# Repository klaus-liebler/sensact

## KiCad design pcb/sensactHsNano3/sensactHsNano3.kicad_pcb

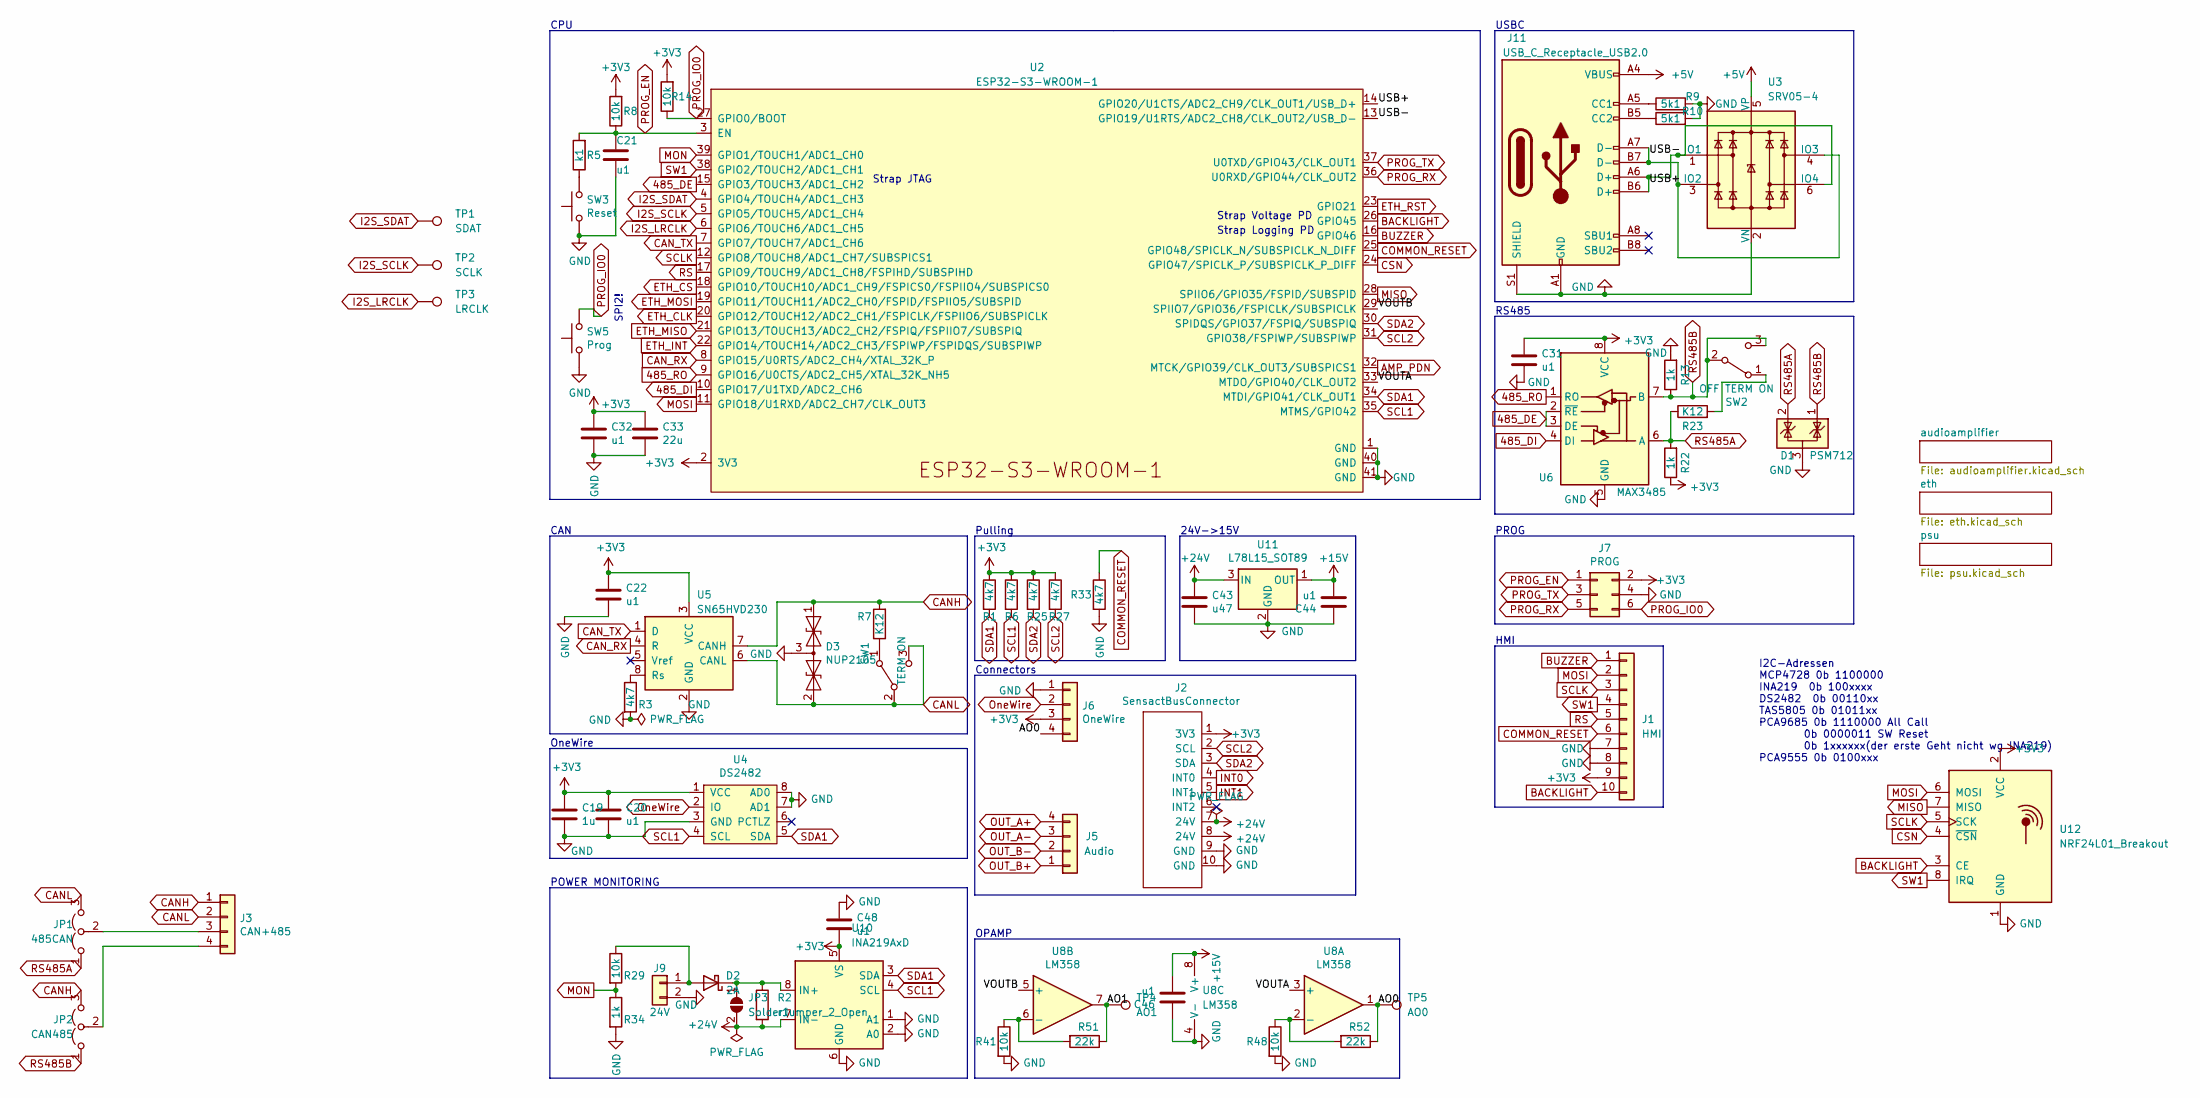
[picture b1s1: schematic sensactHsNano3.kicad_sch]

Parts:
C19: 1u; C_0805_2012Metric_Pad1.18x1.45mm_HandSolder
C20, C48: u1; C_0805_2012Metric_Pad1.18x1.45mm_HandSolder
C21, C22, C31, C32, C44, C46: u1; C_0402_1005Metric
C33: 22u; C_0603_1608Metric
C43: u47; C_0805_2012Metric
D1: PSM712; SOT-23_Handsoldering
D2: 2A; D_SMB_Handsoldering
D3: NUP2105; SOT-23_Handsoldering
J1: HMI; Hirose_FH12-10S-0.5SH_1x10-1MP_P0.50mm_Horizontal
J2: SensactBusConnector; IDC-Header_2x05_P2.54mm_Horizontal_tightCrtYd
J3: CAN+485; PhoenixContact_MC_1,5_4-G-3.5_1x04_P3.50mm_Horizontal_small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
J5: Audio; PhoenixContact_MC_1,5_4-G-3.5_1x04_P3.50mm_Horizontal_small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
J6: OneWire; PhoenixContact_MC_1,5_4-G-3.5_1x04_P3.50mm_Horizontal_small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
J7: PROG; IDC_2x03_P1.27mm_Vertical
J9: 24V; PhoenixContact_MC_1,5_2-G-3.81_1x02_P3.81mm_Horizontal_smal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
J11: USB_C_Receptacle_USB2.0; USB_C_Receptacle_HRO_TYPE-C-31-M-12_smaller
JP1: 485CAN; SolderJumper-3_P1.3mm_Open_RoundedPad1.0x1.5mm_NumberLabels
JP2: CAN485; SolderJumper-3_P1.3mm_Open_RoundedPad1.0x1.5mm_NumberLabels
JP3: SolderJumper_2_Open; SolderJumper-2_P1.3mm_Open_RoundedPad1.0x1.5mm
R1, R3, R6, R25, R27, R33: 4k7; R_0402_1005Metric
R2: r1; R_1206_3216Metric_Pad1.30x1.75mm_HandSolder
R5: k1; R_0402_1005Metric
R7, R23: K12; R_1206_3216Metric_Pad1.30x1.75mm_HandSolder
R8, R14, R29, R41, R48: 10k; R_0402_1005Metric
R9, R10: 5k1; R_0402_1005Metric
R13, R22: 1k; R_0603_1608Metric
R34: 1k; R_0402_1005Metric
R51, R52: 22k; R_0402_1005Metric
SW1: TERM ON; SW_SPDT_PCM12_handsolder
SW2: OFF TERM ON; SW_SPDT_PCM12_handsolder
SW3: Reset; Button_2x4x3,5_handsolder
SW5: Prog; Button_2x4x3,5_handsolder
TP1: SDAT; TestPoint_Pad_2.0x2.0mm
TP2: SCLK; TestPoint_Pad_2.0x2.0mm
TP3: LRCLK; TestPoint_Pad_2.0x2.0mm
TP4: AO1; TestPoint_Pad_2.0x2.0mm
TP5: AO0; TestPoint_Pad_2.0x2.0mm
U2: ESP32-S3-WROOM-1; ESP32-S3-WROOM-1U
U3: SRV05-4; SOT-23-6
U4: DS2482; SOIC-8_3.9x4.9mm_Pitch1.27mm_handsolder
U5: SN65HVD230; SOIC-8_3.9x4.9mm_Pitch1.27mm_handsolder
U6: MAX3485; SOIC-8_3.9x4.9mm_Pitch1.27mm_handsolder
U8: LM358; SOIC-8_3.9x4.9mm_P1.27mm
U10: INA219AxD; SOIC-8_3.9x4.9mm_Pitch1.27mm_handsolder
U11: L78L15_SOT89; SOT-89-3_Handsoldering
U12: NRF24L01_Breakout; nRF24L01_Breakout

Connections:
485_DE: U2.15 (GPIO3/TOUCH3/ADC1_CH2), U6.2 (~RE), U6.3 (DE)
485_DI: U2.10 (GPIO17/U1TXD/ADC2_CH6), U6.4 (DI)
485_RO: U2.9 (GPIO16/U0CTS/ADC2_CH5/XTAL_32K_NH5), U6.1 (RO)
+3V3: C19.1, C20.1, C22.1, C31.2, C32.1, C33.1, C48.2, J1.9, J2.1 (3V3), J6.3, J7.2, R1.1, R6.1, R8.2, R14.2, R22.1, R25.1, R27.1, U2.2 (3V3), U4.1 (VCC), U5.3 (VCC), U6.8 (VCC), U10.5 (VS), U12.2 (VCC); also elsewhere on the board
+5V: J11.A4 (VBUS), J11.A9 (VBUS), J11.B4 (VBUS), J11.B9 (VBUS), U3.5 (VP)
+15V: C44.2, C46.2, U8.8 (V+), U11.1 (OUT)
+24V: C43.1, J2.7 (24V), J2.8 (24V), JP3.2 (B), R2.2, U10.7 (IN-), U11.3 (IN); also elsewhere on the board
/AO0: J6.4, R52.1, TP5.1, U8.1
/AO1: R51.1, TP4.1, U8.7
/USB+: J11.A6 (D+), J11.B6 (D+), U2.14 (GPIO20/U1CTS/ADC2_CH9/CLK_OUT1/USB_D+), U3.1 (IO1), U3.6 (IO4)
/USB-: J11.A7 (D-), J11.B7 (D-), U2.13 (GPIO19/U1RTS/ADC2_CH8/CLK_OUT2/USB_D-), U3.3 (IO2), U3.4 (IO3)
/VOUTA: U2.33 (MTDO/GPIO40/CLK_OUT2), U8.3 (+)
/VOUTB: U2.29 (SPIIO7/GPIO36/FSPICLK/SUBSPICLK), U8.5 (+)
AMP_PDN: U2.32 (MTCK/GPIO39/CLK_OUT3/SUBSPICS1); also elsewhere on the board
BACKLIGHT: J1.10, U2.26 (GPIO45), U12.3 (CE)
BUZZER: J1.1, U2.16 (GPIO46)
CANH: D3.1 (A1), J3.1, JP2.3 (B), R7.2, U5.7 (CANH)
CANL: D3.2 (A2), J3.2, JP1.3 (B), SW1.2 (B), SW1.3 (C), U5.6 (CANL)
CAN_RX: U2.8 (GPIO15/U0RTS/ADC2_CH4/XTAL_32K_P), U5.4 (R)
CAN_TX: U2.7 (GPIO7/TOUCH7/ADC1_CH6), U5.1 (D)
COMMON_RESET: J1.6, R33.1, U2.25 (GPIO48/SPICLK_N/SUBSPICLK_N_DIFF)
CSN: U2.24 (GPIO47/SPICLK_P/SUBSPICLK_P_DIFF), U12.4 (~CSN)
ETH_CLK: U2.20 (GPIO12/TOUCH12/ADC2_CH1/FSPICLK/FSPIIO6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); also elsewhere on the board
ETH_CS: U2.18 (GPIO10/TOUCH10/ADC1_CH9/FSPICS0/FSPIIO4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); also elsewhere on the board
ETH_INT: U2.22 (GPIO14/TOUCH14/ADC2_CH3/FSPIWP/FSPIDQS/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); also elsewhere on the board
ETH_MISO: U2.21 (GPIO13/TOUCH13/ADC2_CH2/FSPIQ/FSPIIO7/S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); also elsewhere on the board
ETH_MOSI: U2.19 (GPIO11/TOUCH11/ADC2_CH0/FSPID/FSPIIO5/S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); also elsewhere on the board
ETH_RST: U2.23 (GPIO21); also elsewhere on the board
GND: C19.2, C20.2, C21.2, C22.2, C31.1, C32.2, C33.2, C43.2, C44.1, C46.1, C48.1, D1.3 (A), D3.3 (common), J1.7, J1.8, J2.9 (GND), J2.10 (GND), J6.1, J7.4, J9.2, J11.A1 (GND), J11.A12 (GND), J11.B1 (GND), J11.B12 (GND), J11.S1 (SHIELD), R3.2, R9.2, R10.2, R13.2, R33.2, R34.2, R41.2, R48.2, SW3.1, SW5.1, U2.1 (GND), U2.40 (GND), U2.41 (GND), U3.2 (VN), U4.3 (GND), U4.7 (AD1), U4.8 (AD0), U5.2 (GND), U6.5 (GND), U8.4 (V-), U10.1 (A1), U10.2 (A0), U10.6 (GND), U11.2 (GND), U12.1 (GND); also elsewhere on the board
I2S_LRCLK: TP3.1, U2.6 (GPIO6/TOUCH6/ADC1_CH5); also elsewhere on the board
I2S_SCLK: TP2.1, U2.5 (GPIO5/TOUCH5/ADC1_CH4); also elsewhere on the board
I2S_SDAT: TP1.1, U2.4 (GPIO4/TOUCH4/ADC1_CH3); also elsewhere on the board
INT0: J2.4 (INT0)
INT1: J2.5 (INT1)
MISO: U2.28 (SPIIO6/GPIO35/FSPID/SUBSPID), U12.7 (MISO)
MON: R29.2, R34.1, U2.39 (GPIO1/TOUCH1/ADC1_CH0)
MOSI: J1.2, U2.11 (GPIO18/U1RXD/ADC2_CH7/CLK_OUT3), U12.6 (MOSI)
unnamed: D2.2 (A), J9.1, R29.1
unnamed: D2.1 (K), JP3.1 (A), R2.1, U10.8 (IN+)
unnamed: J3.3, JP1.2 (C)
unnamed: J3.4, JP2.2 (C)
unnamed: J11.A5 (CC1), R9.1
unnamed: J11.B5 (CC2), R10.1
unnamed: R5.1, SW3.2
unnamed: R7.1, SW1.1 (A)
unnamed: R23.2, SW2.1 (A)
unnamed: R3.1, U5.8 (Rs)
unnamed: R48.1, R52.2, U8.2 (-)
unnamed: R41.1, R51.2, U8.6 (-)
OUT_A+: J5.4; also elsewhere on the board
OUT_A-: J5.3; also elsewhere on the board
OUT_B+: J5.1; also elsewhere on the board
OUT_B-: J5.2; also elsewhere on the board
OneWire: J6.2, U4.2 (IO)
PROG_EN: C21.1, J7.1, R5.2, R8.1, U2.3 (EN)
PROG_IO0: J7.6, R14.1, SW5.2, U2.27 (GPIO0/BOOT)
PROG_RX: J7.5, U2.36 (U0RXD/GPIO44/CLK_OUT2)
PROG_TX: J7.3, U2.37 (U0TXD/GPIO43/CLK_OUT1)
RS: J1.5, U2.17 (GPIO9/TOUCH9/ADC1_CH8/FSPIHD/SUBSPIHD)
RS485A: D1.2 (K), JP1.1 (A), R22.2, R23.1, U6.6 (A)
RS485B: D1.1 (K), JP2.1 (A), R13.1, SW2.2 (B), SW2.3 (C), U6.7 (B)
SCL1: R6.2, U2.35 (MTMS/GPIO42), U4.4 (SCL), U10.4 (SCL); also elsewhere on the board
SCL2: J2.2 (SCL), R27.2, U2.31 (GPIO38/FSPIWP/SUBSPIWP)
SCLK: J1.3, U2.12 (GPIO8/TOUCH8/ADC1_CH7/SUBSPICS1), U12.5 (SCK)
SDA1: R1.2, U2.34 (MTDI/GPIO41/CLK_OUT1), U4.5 (SDA), U10.3 (SDA); also elsewhere on the board
SDA2: J2.3 (SDA), R25.2, U2.30 (SPIDQS/GPIO37/FSPIQ/SUBSPIQ)
SW1: J1.4, U2.38 (GPIO2/TOUCH2/ADC1_CH1), U12.8 (IRQ)

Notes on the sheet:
OneWire
Strap JTAG
Connectors
I2C-Adressen MCP4728 0b 1100000 INA219 0b 100xxxx DS2482 0b 00110xx TAS5805 0b 01011xx PCA9685 0b 1110000 All Call 0b 0000011 SW Reset 0b 1xxxxxx(der erste Geht nicht wg INA219) PCA9555 0b 0100xxx
Strap Voltage PD
HMI
OPAMP
RS485
Pulling
POWER MONITORING
PROG
24V->15V
CAN
SPI2!
USBC
CPU
Strap Logging PD

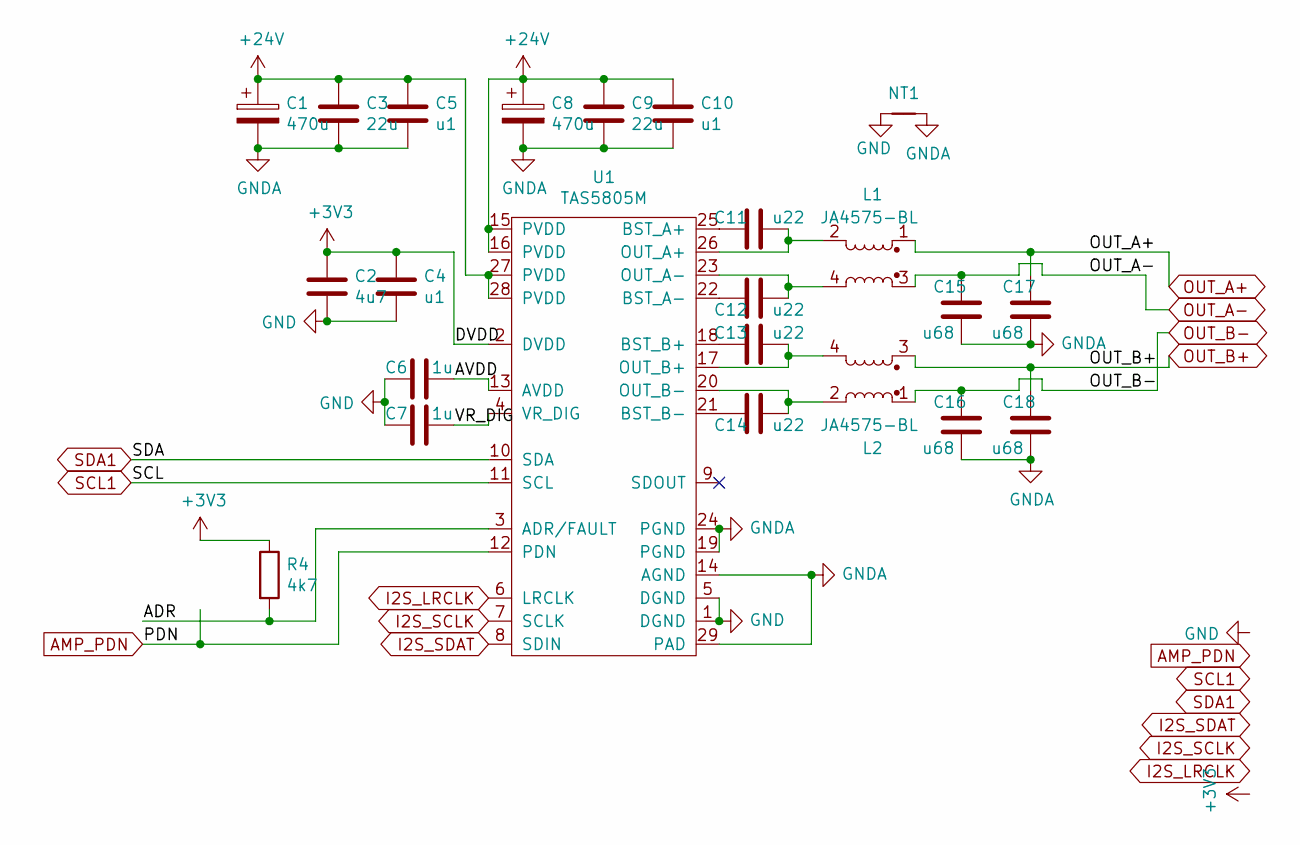
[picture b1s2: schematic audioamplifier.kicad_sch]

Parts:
C1, C8: 470u; CP_Radial_D10.0mm_P3.50mm
C2: 4u7; C_0402_1005Metric
C3, C9: 22u; C_1210_3225Metric_Pad1.33x2.70mm_HandSolder
C4: u1; C_0402_1005Metric
C5, C10: u1; C_0603_1608Metric
C6, C7: 1u; C_0402_1005Metric
C11, C12, C13, C14: u22; C_0603_1608Metric
C15, C16, C17, C18: u68; C_Rect_L7.0mm_W4.5mm_P5.00mm
L1, L2: JA4575-BL
NT1: Net-Tie_2; NetTie-2_SMD_Pad2.0mm
R4: 4k7; R_0402_1005Metric
U1: TAS5805M; HTSSOP-28-1EP_4.4x9.7mm_P0.65mm_EP2.85x5.4mm_ThermalVias

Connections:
+3V3: C2.1, C4.1, R4.1, U1.2 (DVDD); also elsewhere on the board
+24V: C1.1, C3.1, C5.1, C8.1, C9.1, C10.1, U1.15 (PVDD), U1.16 (PVDD), U1.27 (PVDD), U1.28 (PVDD); also elsewhere on the board
/audioamplifier/ADR: R4.2, U1.3 (ADR/FAULT)
/audioamplifier/AVDD: C6.1, U1.13 (AVDD)
/audioamplifier/VR_DIG: C7.1, U1.4 (VR_DIG)
AMP_PDN: U1.12 (PDN); also elsewhere on the board
GND: C2.2, C4.2, C6.2, C7.2, NT1.1, U1.1 (DGND), U1.5 (DGND); also elsewhere on the board
GNDA: C1.2, C3.2, C5.2, C8.2, C9.2, C10.2, C15.1, C16.1, C17.1, C18.1, NT1.2, U1.14 (AGND), U1.19 (PGND), U1.24 (PGND), U1.29 (PAD)
I2S_LRCLK: U1.6 (LRCLK); also elsewhere on the board
I2S_SCLK: U1.7 (SCLK); also elsewhere on the board
I2S_SDAT: U1.8 (SDIN); also elsewhere on the board
unnamed: C11.2, U1.25 (BST_A+)
unnamed: C12.2, U1.22 (BST_A-)
unnamed: C13.2, U1.18 (BST_B+)
unnamed: C14.2, U1.21 (BST_B-)
unnamed: C11.1, L1.2, U1.26 (OUT_A+)
unnamed: C12.1, L1.4, U1.23 (OUT_A-)
unnamed: C13.1, L2.4, U1.17 (OUT_B+)
unnamed: C14.1, L2.2, U1.20 (OUT_B-)
OUT_A+: C17.2, L1.1; also elsewhere on the board
OUT_A-: C15.2, L1.3; also elsewhere on the board
OUT_B+: C18.2, L2.3; also elsewhere on the board
OUT_B-: C16.2, L2.1; also elsewhere on the board
SCL1: U1.11 (SCL); also elsewhere on the board
SDA1: U1.10 (SDA); also elsewhere on the board

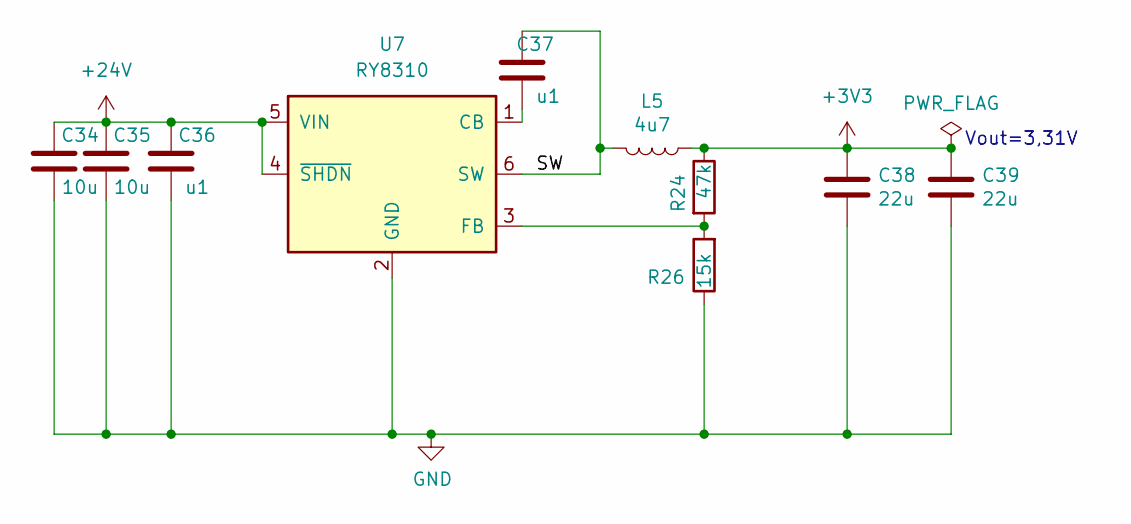
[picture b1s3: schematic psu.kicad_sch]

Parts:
C34, C35: 10u; C_1206_3216Metric
C36, C37: u1; C_0603_1608Metric
C38, C39: 22u; C_0603_1608Metric
L5: 4u7; L_Abracon_ASPI-0630LR
R24: 47k; R_0402_1005Metric
R26: 15k; R_0402_1005Metric
U7: RY8310; SOT-23-6

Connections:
+3V3: C38.1, C39.1, L5.1, R24.1; also elsewhere on the board
+24V: C34.2, C35.2, C36.2, U7.4 (~SHDN), U7.5 (VIN); also elsewhere on the board
/psu/SW: C37.2, L5.2, U7.6 (SW)
GND: C34.1, C35.1, C36.1, C38.2, C39.2, R26.1, U7.2 (GND); also elsewhere on the board
unnamed: C37.1, U7.1 (CB)
unnamed: R24.2, R26.2, U7.3 (FB)

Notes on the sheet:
Vout=3,31V

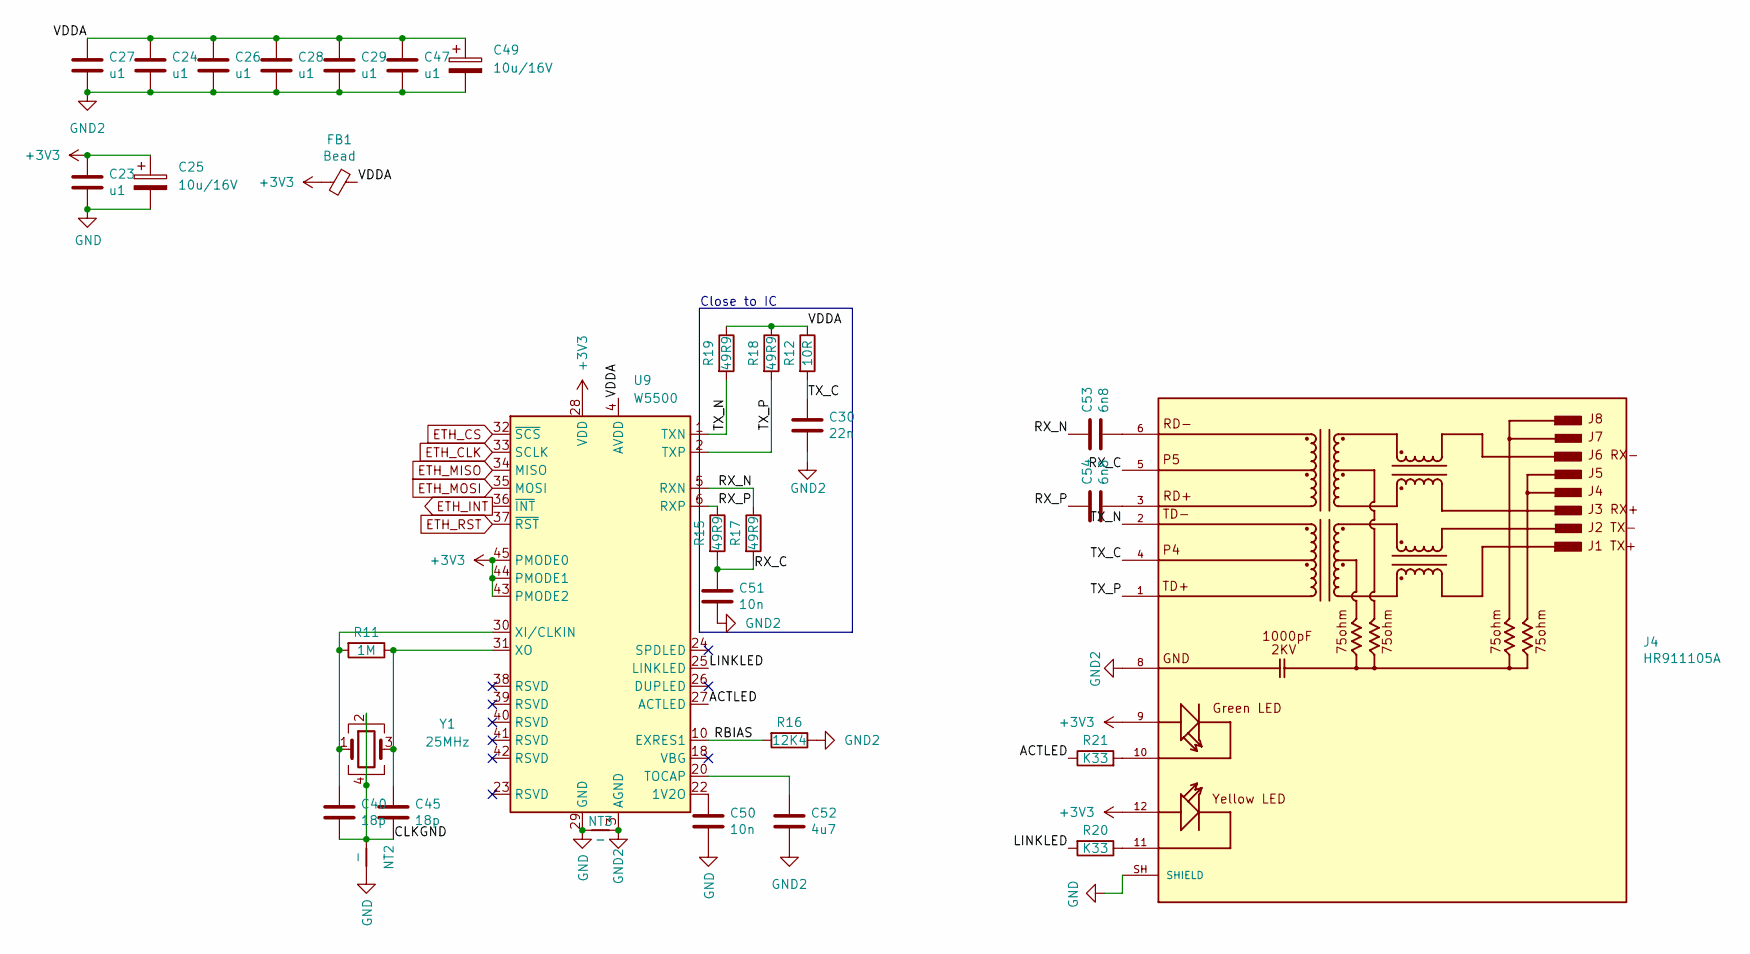
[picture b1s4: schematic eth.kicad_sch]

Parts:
C23, C24, C26, C27, C28, C29, C47: u1; C_0402_1005Metric
C25, C49: 10u/16V; CP_EIA-3216-18_Kemet-A
C30: 22n; C_0402_1005Metric
C40, C45: 18p; C_0402_1005Metric
C50, C51: 10n; C_0402_1005Metric
C52: 4u7; C_0402_1005Metric
C53, C54: 6n8; C_0402_1005Metric
FB1: Bead; L_0805_2012Metric
J4: HR911105A; RJ45_HANRUN_HR911105A; PARTREV A
NT2, NT3: -; NetTie-2_SMD_Pad0.5mm
R11: 1M; R_0402_1005Metric
R12: 10R; R_0402_1005Metric
R15, R17, R18, R19: 49R9; R_0603_1608Metric
R16: 12K4; R_0402_1005Metric
R20, R21: K33; R_0402_1005Metric
U9: W5500; LQFP-48_7x7mm_P0.5mm
Y1: 25MHz; Crystal_SMD_3225-4Pin_3.2x2.5mm

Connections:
+3V3: C23.1, C25.1, FB1.2, J4.9, J4.12, U9.28 (VDD), U9.43 (PMODE2), U9.44 (PMODE1), U9.45 (PMODE0); also elsewhere on the board
/eth/ACTLED: R21.1, U9.27 (ACTLED)
/eth/CLKGND: C40.2, C45.2, NT2.2, Y1.2, Y1.4
/eth/LINKLED: R20.2, U9.25 (LINKLED)
/eth/RBIAS: R16.2, U9.10 (EXRES1)
/eth/RX_C: C51.1, J4.5, R15.2, R17.2
/eth/RX_N: C53.1, R17.1, U9.5 (RXN)
/eth/RX_P: C54.1, R15.1, U9.6 (RXP)
/eth/TX_C: C30.1, J4.4, R12.2
/eth/TX_N: J4.2, R19.2, U9.1 (TXN)
/eth/TX_P: J4.1, R18.2, U9.2 (TXP)
/eth/VDDA: C24.1, C26.1, C27.1, C28.1, C29.1, C47.1, C49.1, FB1.1, R12.1, R18.1, R19.1, U9.4 (AVDD), U9.8 (AVDD), U9.11 (AVDD), U9.15 (AVDD), U9.17 (AVDD), U9.21 (AVDD)
ETH_CLK: U9.33 (SCLK); also elsewhere on the board
ETH_CS: U9.32 (~SCS); also elsewhere on the board
ETH_INT: U9.36 (~INT); also elsewhere on the board
ETH_MISO: U9.34 (MISO); also elsewhere on the board
ETH_MOSI: U9.35 (MOSI); also elsewhere on the board
ETH_RST: U9.37 (~RST); also elsewhere on the board
GND: C23.2, C25.2, C50.2, J4.SH (SHIELD), NT2.1, NT3.2, U9.29 (GND); also elsewhere on the board
GND2: C24.2, C26.2, C27.2, C28.2, C29.2, C30.2, C47.2, C49.2, C51.2, C52.2, J4.8, NT3.1, R16.1, U9.3 (AGND), U9.9 (AGND), U9.14 (AGND), U9.16 (AGND), U9.19 (AGND), U9.48 (AGND)
unnamed: C53.2, J4.6
unnamed: C54.2, J4.3
unnamed: J4.10, R21.2
unnamed: J4.11, R20.1
unnamed: C50.1, U9.22 (1V2O)
unnamed: C52.1, U9.20 (TOCAP)
unnamed: C40.1, R11.2, U9.30 (XI/CLKIN), Y1.1
unnamed: C45.1, R11.1, U9.31 (XO), Y1.3

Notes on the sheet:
Close to IC

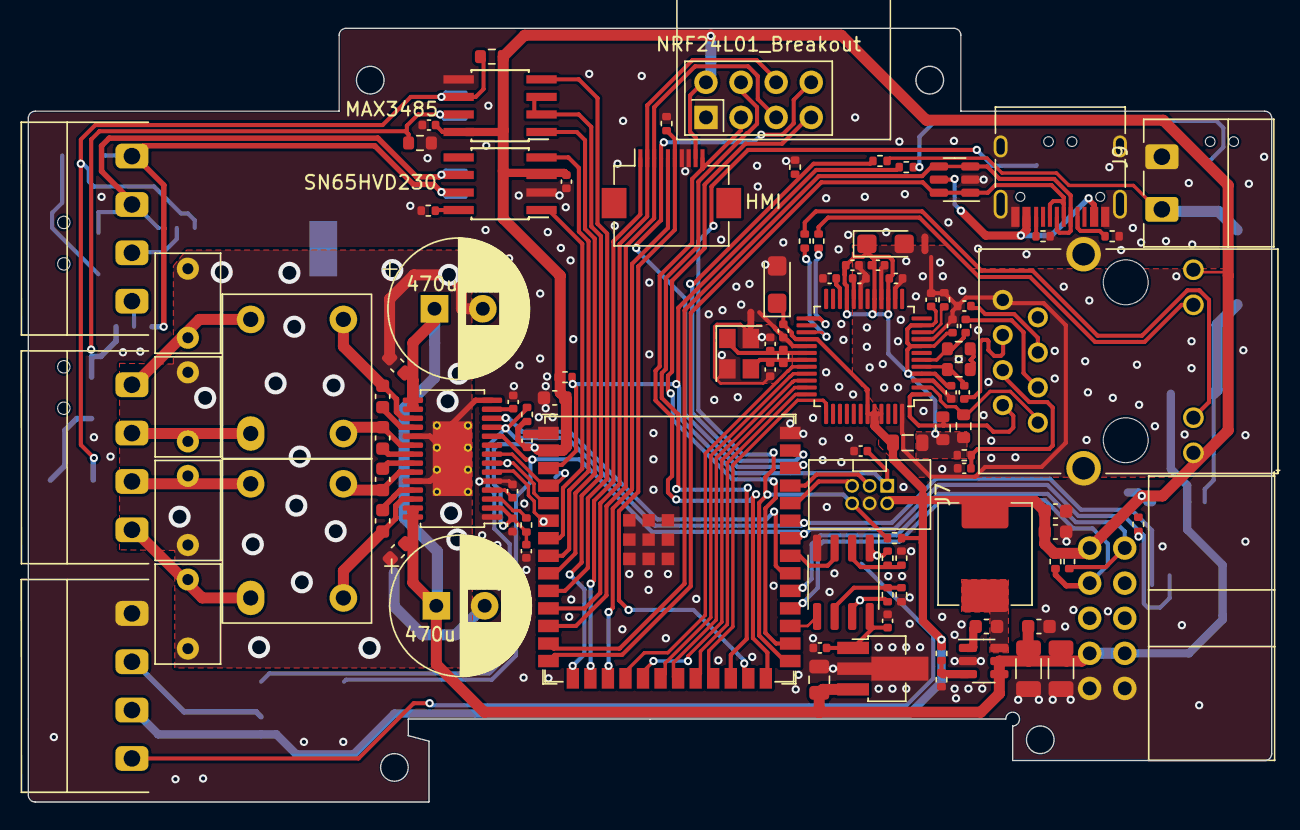
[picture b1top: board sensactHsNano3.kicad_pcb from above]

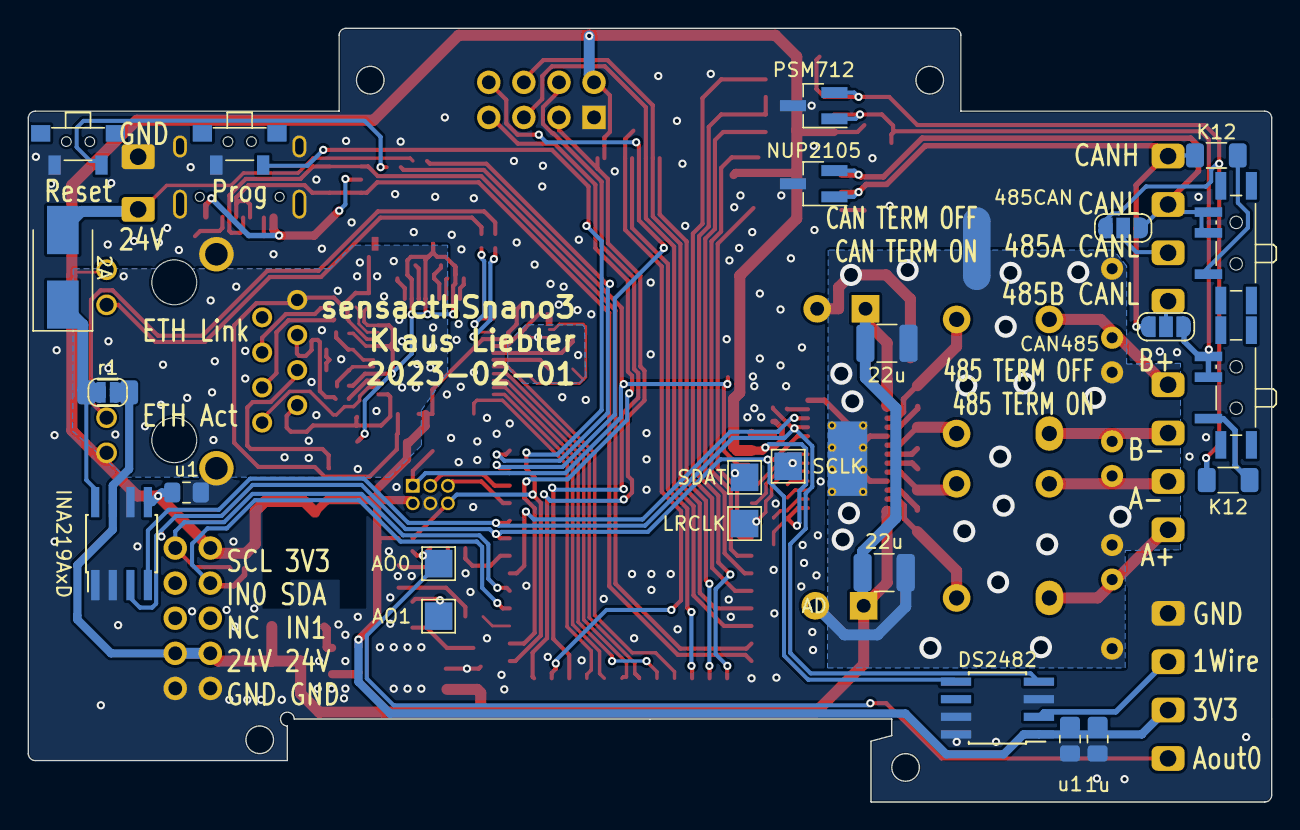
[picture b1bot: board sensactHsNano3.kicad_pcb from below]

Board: 2 copper layers, 90.0 x 56.0 mm, 130 parts (26 on the bottom side), 100 nets.

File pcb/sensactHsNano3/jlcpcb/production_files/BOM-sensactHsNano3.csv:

Comment,Designator,Footprint,LCSC
Bead,FB1,L_0805_2012Metric,C1017
12K4,R16,R_0402_1005Metric,C11692
1k,R34,R_0402_1005Metric,C11702
SN65HVD230,U5,SOIC-8_3.9x4.9mm_Pitch1.27mm_handsolder,C12084
10u,"C34,C35",C_1206_3216Metric,C13585
u47,C43,C_0805_2012Metric,C13967
u1,"C10,C36,C37,C5",C_0603_1608Metric,C14663
10n,"C50,C51",C_0402_1005Metric,C15195
22n,C30,C_0402_1005Metric,C1532
6n8,"C53,C54",C_0402_1005Metric,C1542
18p,"C40,C45",C_0402_1005Metric,C1549
USB_C_Receptacle_USB2.0,J11,USB_C_Receptacle_HRO_TYPE-C-31-M-12_smaller,C165948
u22,"C11,C12,C13,C14",C_0603_1608Metric,C21120
1k,"R13,R22",R_0603_1608Metric,C21190
49R9,"R15,R17,R18,R19",R_0603_1608Metric,C23185
4u7,"C2,C52",C_0402_1005Metric,C23733
k1,R5,R_0402_1005Metric,C25076
10R,R12,R_0402_1005Metric,C25077
K33,"R20,R21",R_0402_1005Metric,C25104
10k,"R14,R29,R41,R48,R8",R_0402_1005Metric,C25744
15k,R26,R_0402_1005Metric,C25756
22k,"R51,R52",R_0402_1005Metric,C25768
47k,R24,R_0402_1005Metric,C25792
4k7,"R1,R25,R27,R3,R33,R4,R6",R_0402_1005Metric,C25900
5k1,"R10,R9",R_0402_1005Metric,C25905
1M,R11,R_0402_1005Metric,C26083
HMI,J1,Hirose_FH12-10S-0.5SH_1x10-1MP_P0.50mm_Horizontal,C262659
ESP32-S3-WROOM-1,U2,ESP32-S3-WROOM-1U,C3013944
u1,"C21,C22,C23,C24,C26,C27,C28,C29,C31,C32,C4,C44,C46,C47",C_0402_1005Metric,C307331
W5500,U9,LQFP-48_7x7mm_P0.5mm,C32843
RY8310,U7,SOT-23-6,C370876
4u7,L5,L_Abracon_ASPI-0630LR,C408447
TAS5805M,U1,HTSSOP-28-1EP_4.4x9.7mm_P0.65mm_EP2.85x5.4mm_ThermalVias,C478472
1u,"C6,C7",C_0402_1005Metric,C52923
22u,"C33,C38,C39",C_0603_1608Metric,C59461
10u/16V,"C25,C49",CP_EIA-3216-18_Kemet-A,C7171
22u,"C3,C9",C_1210_3225Metric_Pad1.33x2.70mm_HandSolder,C778721
LM358,U8,SOIC-8_3.9x4.9mm_P1.27mm,C7950
SRV05-4,U3,SOT-23-6,C85364
MAX3485,U6,SOIC-8_3.9x4.9mm_Pitch1.27mm_handsolder,C8963
25MHz,Y1,Crystal_SMD_3225-4Pin_3.2x2.5mm,C9006
u68,C15,C_Rect_L7.0mm_W4.5mm_P5.00mm,
u68,C16,C_Rect_L7.0mm_W4.5mm_P5.00mm,
u68,C17,C_Rect_L7.0mm_W4.5mm_P5.00mm,
u68,C18,C_Rect_L7.0mm_W4.5mm_P5.00mm,
K12,R7,R_1206_3216Metric_Pad1.30x1.75mm_HandSolder,
OFF TERM  ON,SW2,SW_SPDT_PCM12_handsolder,
TERM ON,SW1,SW_SPDT_PCM12_handsolder,
PSM712,D1,SOT-23_Handsoldering,
NUP2105,D3,SOT-23_Handsoldering,
K12,R23,R_1206_3216Metric_Pad1.30x1.75mm_HandSolder,
Reset,SW3,"Button_2x4x3,5_handsolder",
2A,D2,D_SMB_Handsoldering,
1u,C19,C_0805_2012Metric_Pad1.18x1.45mm_HandSolder,
CAN+485,J3,"PhoenixContact_MC_1,5_4-G-3.5_1x04_P3.50mm_Horizontal_smallerCourtyard",
HR911105A,J4,RJ45_HANRUN_HR911105A,
u1,C20,C_0805_2012Metric_Pad1.18x1.45mm_HandSolder,
JA4575-BL,L2,JA4575-BL,
Audio,J5,"PhoenixContact_MC_1,5_4-G-3.5_1x04_P3.50mm_Horizontal_smallerCourtyard",
JA4575-BL,L1,JA4575-BL,
SensactBusConnector,J2,IDC-Header_2x05_P2.54mm_Horizontal_tightCrtYd,
DS2482,U4,SOIC-8_3.9x4.9mm_Pitch1.27mm_handsolder,
470u,C8,CP_Radial_D10.0mm_P3.50mm,
470u,C1,CP_Radial_D10.0mm_P3.50mm,
Net-Tie_2,NT1,NetTie-2_SMD_Pad2.0mm,
PROG,J7,IDC_2x03_P1.27mm_Vertical,
OneWire,J6,"PhoenixContact_MC_1,5_4-G-3.5_1x04_P3.50mm_Horizontal_smallerCourtyard",
L78L15_SOT89,U11,SOT-89-3_Handsoldering,
24V,J9,"PhoenixContact_MC_1,5_2-G-3.81_1x02_P3.81mm_Horizontal",
-,NT3,NetTie-2_SMD_Pad0.5mm,
NRF24L01_Breakout,U12,nRF24L01_Breakout,
-,NT2,NetTie-2_SMD_Pad0.5mm,
SDAT,TP1,TestPoint_Pad_2.0x2.0mm,
SolderJumper_2_Open,JP3,SolderJumper-2_P1.3mm_Open_RoundedPad1.0x1.5mm,
LRCLK,TP3,TestPoint_Pad_2.0x2.0mm,
AO0,TP5,TestPoint_Pad_2.0x2.0mm,
485CAN,JP1,SolderJumper-3_P1.3mm_Open_RoundedPad1.0x1.5mm_NumberLabels,
SCLK,TP2,TestPoint_Pad_2.0x2.0mm,
Prog,SW5,"Button_2x4x3,5_handsolder",
AO1,TP4,TestPoint_Pad_2.0x2.0mm,
CAN485,JP2,SolderJumper-3_P1.3mm_Open_RoundedPad1.0x1.5mm_NumberLabels,
INA219AxD,U10,SOIC-8_3.9x4.9mm_Pitch1.27mm_handsolder,
r1,R2,R_1206_3216Metric_Pad1.30x1.75mm_HandSolder,
u1,C48,C_0805_2012Metric_Pad1.18x1.45mm_HandSolder,

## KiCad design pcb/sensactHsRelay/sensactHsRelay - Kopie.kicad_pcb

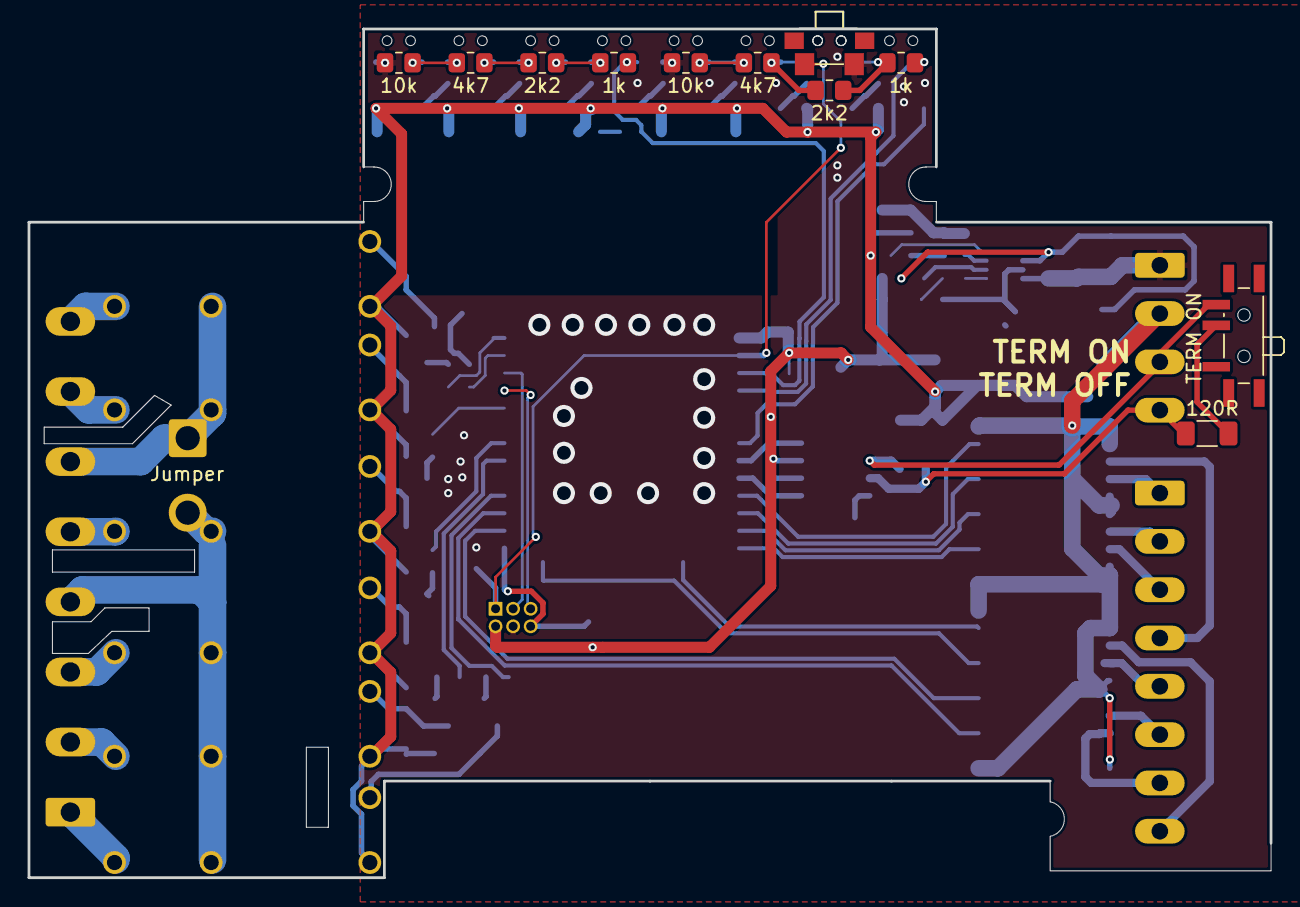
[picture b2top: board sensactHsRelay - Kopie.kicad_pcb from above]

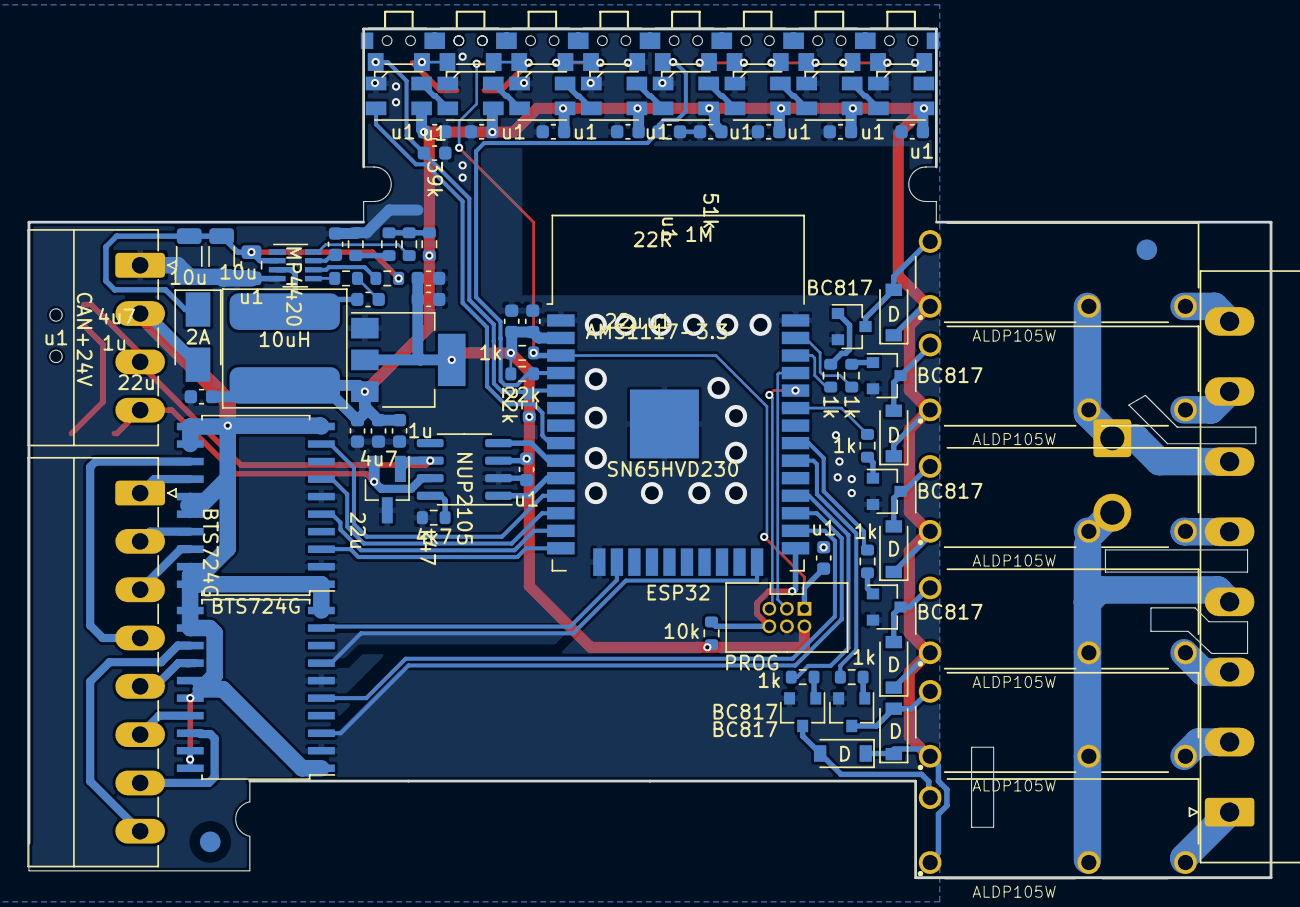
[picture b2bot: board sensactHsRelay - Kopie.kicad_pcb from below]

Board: 2 copper layers, 90.0 x 61.5 mm, 103 parts (91 on the bottom side), 81 nets.

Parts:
C1, C2, C3, C4, C5, C6, C7, C8, C9, C10, C22, C32, C36, C37, C40: u1; C_0603_1608Metric
C11, C14: 4u7; C_0603_1608Metric
C12, C13: 1u; C_0603_1608Metric
C31, C34: 10u; C_1206_3216Metric
C33, C38, C39: 22u; C_0603_1608Metric
C35: u1; C_0805_2012Metric
D1, D2, D5, D6, D7, D8: D; D_SOD-123
D3: NUP2105; SOT-23_Handsoldering
D4: 2A; D_SMA
FID1, FID2: Fiducial; Fiducial_1.5mm_Mask3mm
J1: PROG; IDC_2x03_P1.27mm_Vertical
J2: Conn_01x08; PhoenixContact_MC_1,5_8-G-3.5_1x08_P3.50mm_Horizontal
J3: CAN+24V; PhoenixContact_MC_1,5_4-G-3.5_1x04_P3.50mm_Horizontal
J4: Conn_01x08; PhoenixContact_MSTBA_2,5_8-G-5,08_1x08_P5.08mm_Horizontal
JP3: Jumper; SolderWire-1sqmm_1x02_P5.4mm_D1.4mm_OD2.7mm
K1, K2, K3, K4, K5, K6: ALDP105W; RELAY_ALDP105W
L5: 10uH; ASPIAIG-Q8080
LED1, LED2, LED3, LED4, LED5, LED6, LED7, LED8: SK6812; LED_SK6812MINI_PLCC4_3.5x3.5mm_P1.75mm
PB1, PB2, PB3, PB4, PB5, PB6, PB7, PB8: PB; Button_2x4x3,5
Q1, Q2, Q3, Q4, Q5, Q6: BC817; SOT-23
R2, R10: 22k; R_0603_1608Metric
R3: 4k7; R_0603_1608Metric
R4, R12: 10k; R_0805_2012Metric_Pad1.20x1.40mm_HandSolder
R5, R14: 4k7; R_0805_2012Metric_Pad1.20x1.40mm_HandSolder
R7: 120R; R_1206_3216Metric_Pad1.30x1.75mm_HandSolder
R8, R15: 2k2; R_0805_2012Metric_Pad1.20x1.40mm_HandSolder
R9, R16: 1k; R_0805_2012Metric_Pad1.20x1.40mm_HandSolder
R11, R13, R17, R18, R19, R20, R21: 1k; R_0603_1608Metric
R22: 1M; R_0603_1608Metric
R23: 51k; R_0603_1608Metric
R24: 22R; R_0603_1608Metric
R25: 10k; R_0603_1608Metric
R26: k47; R_0603_1608Metric
R34: 6k8; R_0603_1608Metric
R35: 39k; R_0603_1608Metric
SW1: TERM ON; SW_SPDT_PCM12_handsolder
SW3: Reset; Button_2x4x3,5_handsolder
U1: AMS1117-3.3; SOT-223-3_TabPin2
U2, U4: BTS724G; Infineon_PG-DSO-20-32
U3: ESP32; ESP32-WROOM-32
U5: SN65HVD230; SOIC-8_3.9x4.9mm_P1.27mm
U7: MP4420; TSOT-23-8

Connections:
+3V3: C13.1, C14.1, C22.1, C32.1, C33.1, J1.2, R2.2, R10.2, R11.1, R25.1, U1.2, U3.2, U5.3
+5V: C1.1, C2.1, C3.1, C4.1, C5.1, C6.1, C7.1, C8.1, C11.1, C12.1, C38.1, C39.1, D1.1, D2.1, D5.1, D6.1, D7.1, D8.1, K1.A1, K2.A1, K3.A1, K4.A1, K5.A1, K6.A1, L5.1, LED1.3, LED2.3, LED3.3, LED4.3, LED5.3, LED6.3, LED7.3, LED8.3, R35.1, U1.3
+24V: C31.2, C34.2, C35.2, D4.1, R22.1, U7.2
/EXT1: U3.12, U4.7
/EXT2: U3.13, U4.5
/EXT3: U3.14, U4.3
/EXT4: U3.11, U4.9
/EXT5: U2.7, U3.24
/EXT6: U2.5, U3.26
/EXT7: U2.3, U3.27
/EXT8: U2.9, U3.16
/psu/SW: C37.1, L5.2, U7.3
CANH: D3.2, J3.4, R7.2, U5.7
CANL: D3.1, J3.3, SW1.3, U5.6
CAN_RX: U3.9, U5.4
CAN_TX: U3.10, U5.1
GND: C1.2, C2.2, C3.2, C4.2, C5.2, C6.2, C7.2, C8.2, C9.1, C10.1, C11.2, C12.2, C13.2, C14.2, C22.2, C31.1, C32.2, C33.2, C34.1, C35.1, C36.1, C38.2, C39.2, C40.2, D3.3, J1.4, J3.1, LED1.1, LED2.1, LED3.1, LED4.1, LED5.1, LED6.1, LED7.1, LED8.1, PB1.2, PB5.2, Q1.2, Q2.2, Q3.2, Q4.2, Q5.2, Q6.2, R3.2, R4.1, R12.1, R34.1, SW3.2, U1.1, U2.2, U2.6, U3.1, U3.15, U3.38, U3.39, U4.2, U4.6, U5.2, U7.4
K1: R13.2, U3.36
K2: R17.2, U3.37
K3: R18.2, U3.33
K4: R19.2, U3.31
K5: R20.2, U3.30
K6: R21.2, U3.28
KEYS1: C9.2, PB8.1, R2.1, R9.2, U3.5
KEYS2: C10.2, PB4.1, R10.1, R16.2, U3.4
LEDS: LED1.2, U3.8
unnamed: C36.2, U7.7
unnamed: C37.2, R24.1
unnamed: D1.2, K1.A2, Q1.3
unnamed: D2.2, K2.A2, Q2.3
unnamed: D5.2, K3.A2, Q3.3
unnamed: D6.2, K4.A2, Q4.3
unnamed: D7.2, K5.A2, Q5.3
unnamed: D8.2, K6.A2, Q6.3
unnamed: J2.1, U4.14
unnamed: J2.2, U4.17
unnamed: J2.3, U4.18
unnamed: J2.4, U4.13
unnamed: J2.5, U2.14
unnamed: J2.6, U2.17
unnamed: J2.7, U2.18
unnamed: J2.8, U2.13
unnamed: J4.1, K6.14
unnamed: J4.2, K5.14
unnamed: J4.3, K4.14
unnamed: J4.4, JP3.2, K3.11, K4.11, K5.11, K6.11
unnamed: J4.5, K3.14
unnamed: J4.6, JP3.1, K1.11, K2.11
unnamed: J4.7, K2.14
unnamed: J4.8, K1.14
unnamed: LED1.4, LED2.2
unnamed: LED2.4, LED3.2
unnamed: LED3.4, LED4.2
unnamed: LED4.4, LED5.2
unnamed: LED5.4, LED6.2
unnamed: LED6.4, LED7.2
unnamed: LED7.4, LED8.2
unnamed: PB1.1, PB2.2, R12.2, R14.1
unnamed: PB2.1, PB3.2, R14.2, R15.1
unnamed: PB3.1, PB4.2, R15.2, R16.1
unnamed: PB5.1, PB6.2, R4.2, R5.1
unnamed: PB6.1, PB7.2, R5.2, R8.1
unnamed: PB7.1, PB8.2, R8.2, R9.1
unnamed: Q1.1, R13.1
unnamed: Q2.1, R17.1
unnamed: Q3.1, R18.1
unnamed: Q4.1, R19.1
unnamed: Q5.1, R20.1
unnamed: Q6.1, R21.1
unnamed: R3.1, U5.8
unnamed: R7.1, SW1.2
unnamed: R22.2, U7.6
unnamed: R23.1, R26.2, R35.2
unnamed: R23.2, U7.8
unnamed: R24.2, U7.5
unnamed: R26.1, R34.2
PROG_EN: C40.1, J1.1, R11.2, SW3.1, U3.3
PROG_IO0: J1.6, R25.2, U3.25
PROG_RX: J1.5, U3.34
PROG_TX: J1.3, U3.35
VDC: D4.2, J3.2, U2.1, U2.10, U2.11, U2.12, U2.15, U2.16, U2.19, U2.20, U4.1, U4.10, U4.11, U4.12, U4.15, U4.16, U4.19, U4.20
